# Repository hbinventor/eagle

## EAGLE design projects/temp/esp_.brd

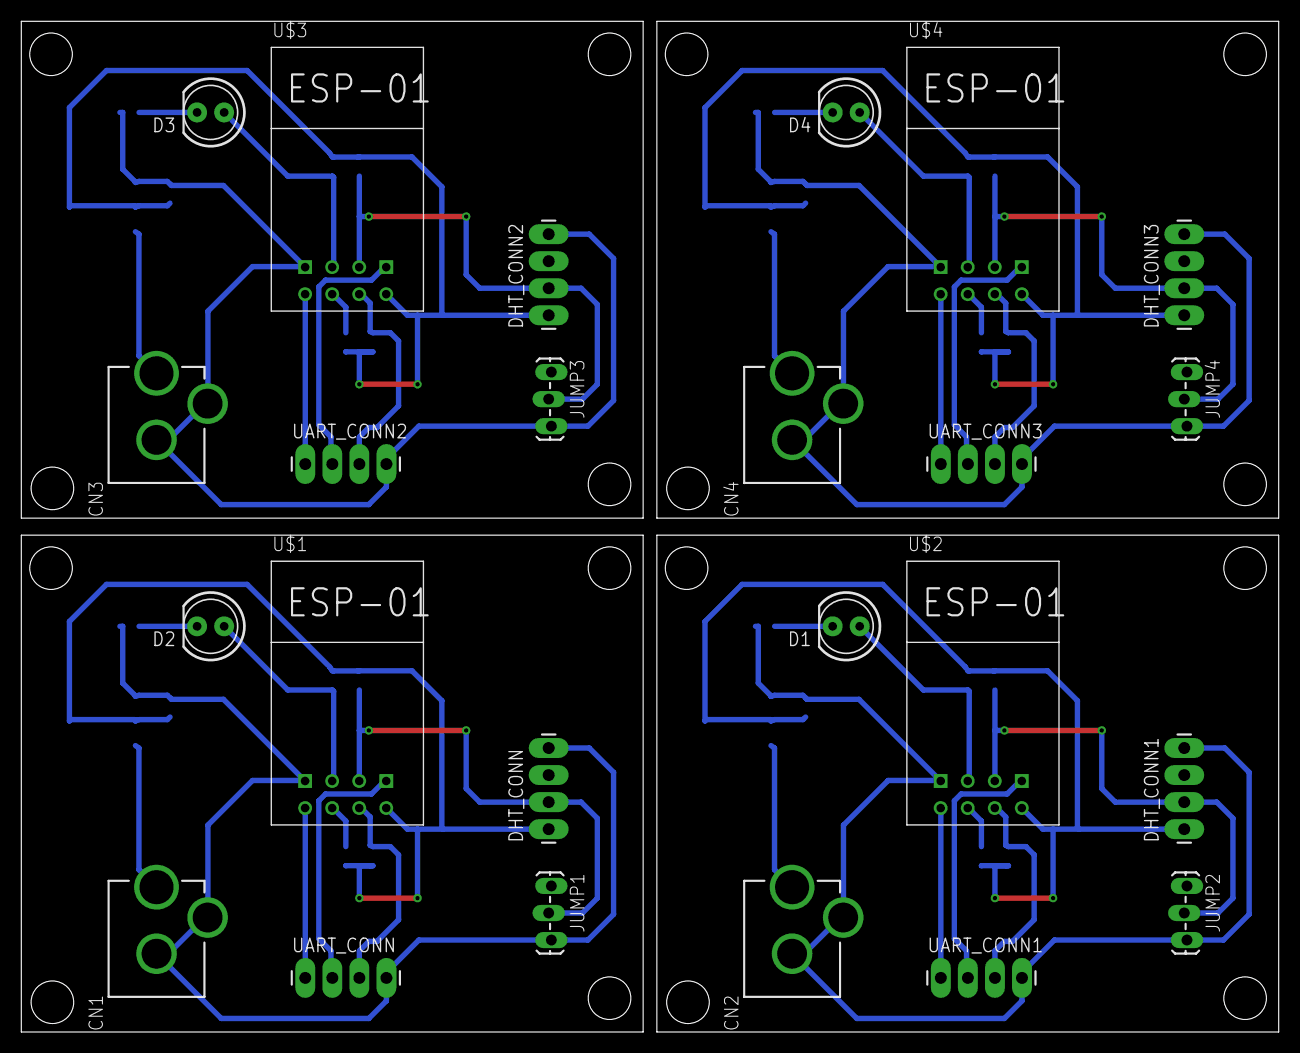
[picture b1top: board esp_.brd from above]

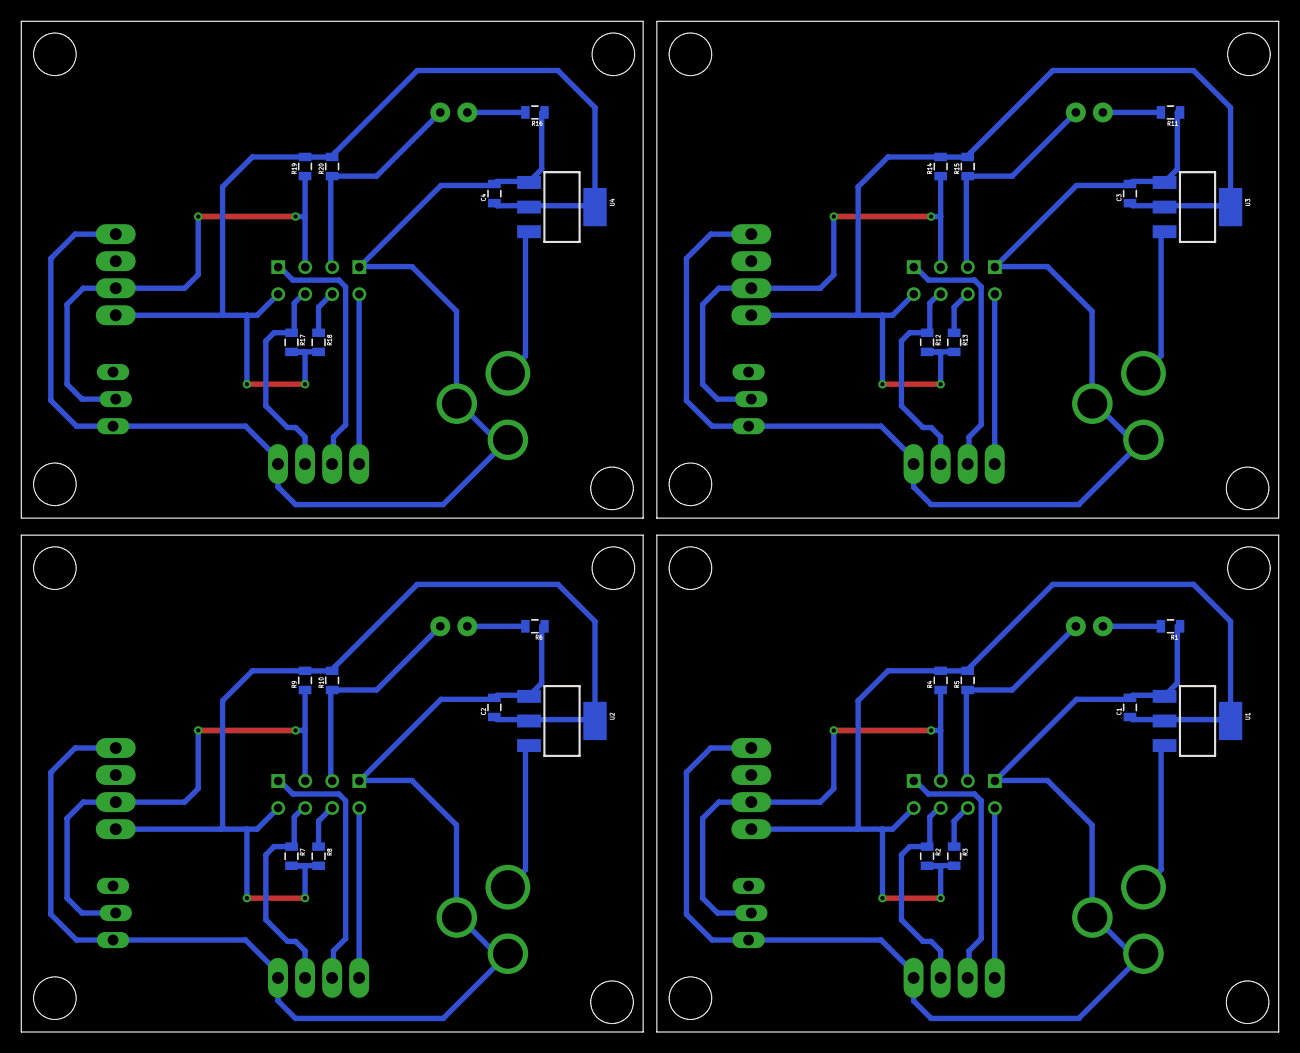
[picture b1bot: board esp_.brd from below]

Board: 2 copper layers, 118.1 x 94.9 mm, 52 parts (28 on the bottom side), 40 nets.

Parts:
C1, C2, C3, C4: 0805
CN1, CN2, CN3, CN4: DCJACK_2MM_PTH
D1, D2, D3, D4: LED5MM
DHT_CONN, DHT_CONN1, DHT_CONN2, DHT_CONN3: 1X04_LONGPADS
JUMP1, JUMP2, JUMP3, JUMP4: 1X03_LOCK_LONGPADS
R1, R6, R11, R16: 100; 0805
R2, R3, R4, R5, R7, R8, R9, R10, R12, R13, R14, R15, R17, R18, R19, R20: 4.7k; 0805
U1, U2, U3, U4: SOT223
U$1, U$2, U$3, U$4: ESP01
UART_CONN, UART_CONN1, UART_CONN2, UART_CONN3: 1X04_LONGPADS

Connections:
3.3V: C1.1, DHT_CONN.1, R2.2, R3.2, R4.2, R5.2, U1.2, U1.4, U$1.VCC
3.3V1: C2.1, DHT_CONN1.1, R7.2, R8.2, R9.2, R10.2, U2.2, U2.4, U$2.VCC
3.3V2: C3.1, DHT_CONN2.1, R12.2, R13.2, R14.2, R15.2, U3.2, U3.4, U$3.VCC
3.3V3: C4.1, DHT_CONN3.1, R17.2, R18.2, R19.2, R20.2, U4.2, U4.4, U$4.VCC
CH_PD: R3.1, U$1.CH_PD
CH_PD1: R8.1, U$2.CH_PD
CH_PD2: R13.1, U$3.CH_PD
CH_PD3: R18.1, U$4.CH_PD
GND: C1.2, CN1.GND, CN1.GNDBREAK, DHT_CONN.4, JUMP1.3, R1.1, U1.1, U$1.GND, UART_CONN.4
GND1: C2.2, CN2.GND, CN2.GNDBREAK, DHT_CONN1.4, JUMP2.3, R6.1, U2.1, U$2.GND, UART_CONN1.4
GND2: C3.2, CN3.GND, CN3.GNDBREAK, DHT_CONN2.4, JUMP3.3, R11.1, U3.1, U$3.GND, UART_CONN2.4
GND3: C4.2, CN4.GND, CN4.GNDBREAK, DHT_CONN3.4, JUMP4.3, R16.1, U4.1, U$4.GND, UART_CONN3.4
GPIO0: DHT_CONN.2, JUMP1.2, R4.1, U$1.GPIO0
GPIO1: DHT_CONN1.2, JUMP2.2, R9.1, U$2.GPIO0
GPIO2: D2.A, R5.1, U$1.GPIO2
GPIO3: D1.A, R10.1, U$2.GPIO2
GPIO4: DHT_CONN2.2, JUMP3.2, R14.1, U$3.GPIO0
GPIO5: D3.A, R15.1, U$3.GPIO2
GPIO6: DHT_CONN3.2, JUMP4.2, R19.1, U$4.GPIO0
GPIO7: D4.A, R20.1, U$4.GPIO2
unnamed: D2.K, R1.2
unnamed: D1.K, R6.2
unnamed: D3.K, R11.2
unnamed: D4.K, R16.2
RESET: R2.1, U$1.RST, UART_CONN.3
RESET1: R7.1, U$2.RST, UART_CONN1.3
RESET2: R12.1, U$3.RST, UART_CONN2.3
RESET3: R17.1, U$4.RST, UART_CONN3.3
RX: U$1.RX, UART_CONN.2
RX1: U$2.RX, UART_CONN1.2
RX2: U$3.RX, UART_CONN2.2
RX3: U$4.RX, UART_CONN3.2
TX: U$1.TX, UART_CONN.1
TX1: U$2.TX, UART_CONN1.1
TX2: U$3.TX, UART_CONN2.1
TX3: U$4.TX, UART_CONN3.1
VCC: CN1.PWR, U1.3
VCC1: CN2.PWR, U2.3
VCC2: CN3.PWR, U3.3
VCC3: CN4.PWR, U4.3

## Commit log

2016-08-29 :boom::camel: Added .gitattributes
2016-09-02 layout

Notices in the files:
parts and their libraries:
SparkFun-Capacitors: Licensing: Creative Commons ShareAlike 4.0 International - https://creativecommons.org/licenses/by-sa/4.0
